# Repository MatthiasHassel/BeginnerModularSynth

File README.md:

# BeginnerModularSynth
DIY Modular Synth based on the Bela Board

I built this DIY Modular Synth for my bachelor thesis in February 2022. It is based on the Bela Board from the Augmented Instruments Laboratory in London and Eurorack compatible, where only voltages between 0V and +5V are evaluated correctly at the moment. However voltages beyond that limit won't harm the hardware and will be interpreted as 0V or +5V

With a "Default Patch" option it is possible to activate a fixed signal flow, where no patching is needed.

A lot of the code is inspired by materials based on a Master’s module “Music and Audio Programming”, taught by Dr Andrew McPherson in the School of Electronic Engineering and Computer Science. Thank you for making this lecture accessible for the public! 

C++ Realtime Programming with Bela:
https://www.youtube.com/watch?v=aVLRUyPBBJk&list=PLCrgFeG6pwQmdbB6l3ehC8oBBZbatVoz3

The Audio itself is not patchable for now, meaning the Audio signal flow is always Oscillator Out -> Filter In -> Filter Out -> Mixer In -> Mixer Out
For a next prototype however it is planned to change this to complete the modularity.

It's still a "work in progress" thing so I am happy about feedback and improvements!

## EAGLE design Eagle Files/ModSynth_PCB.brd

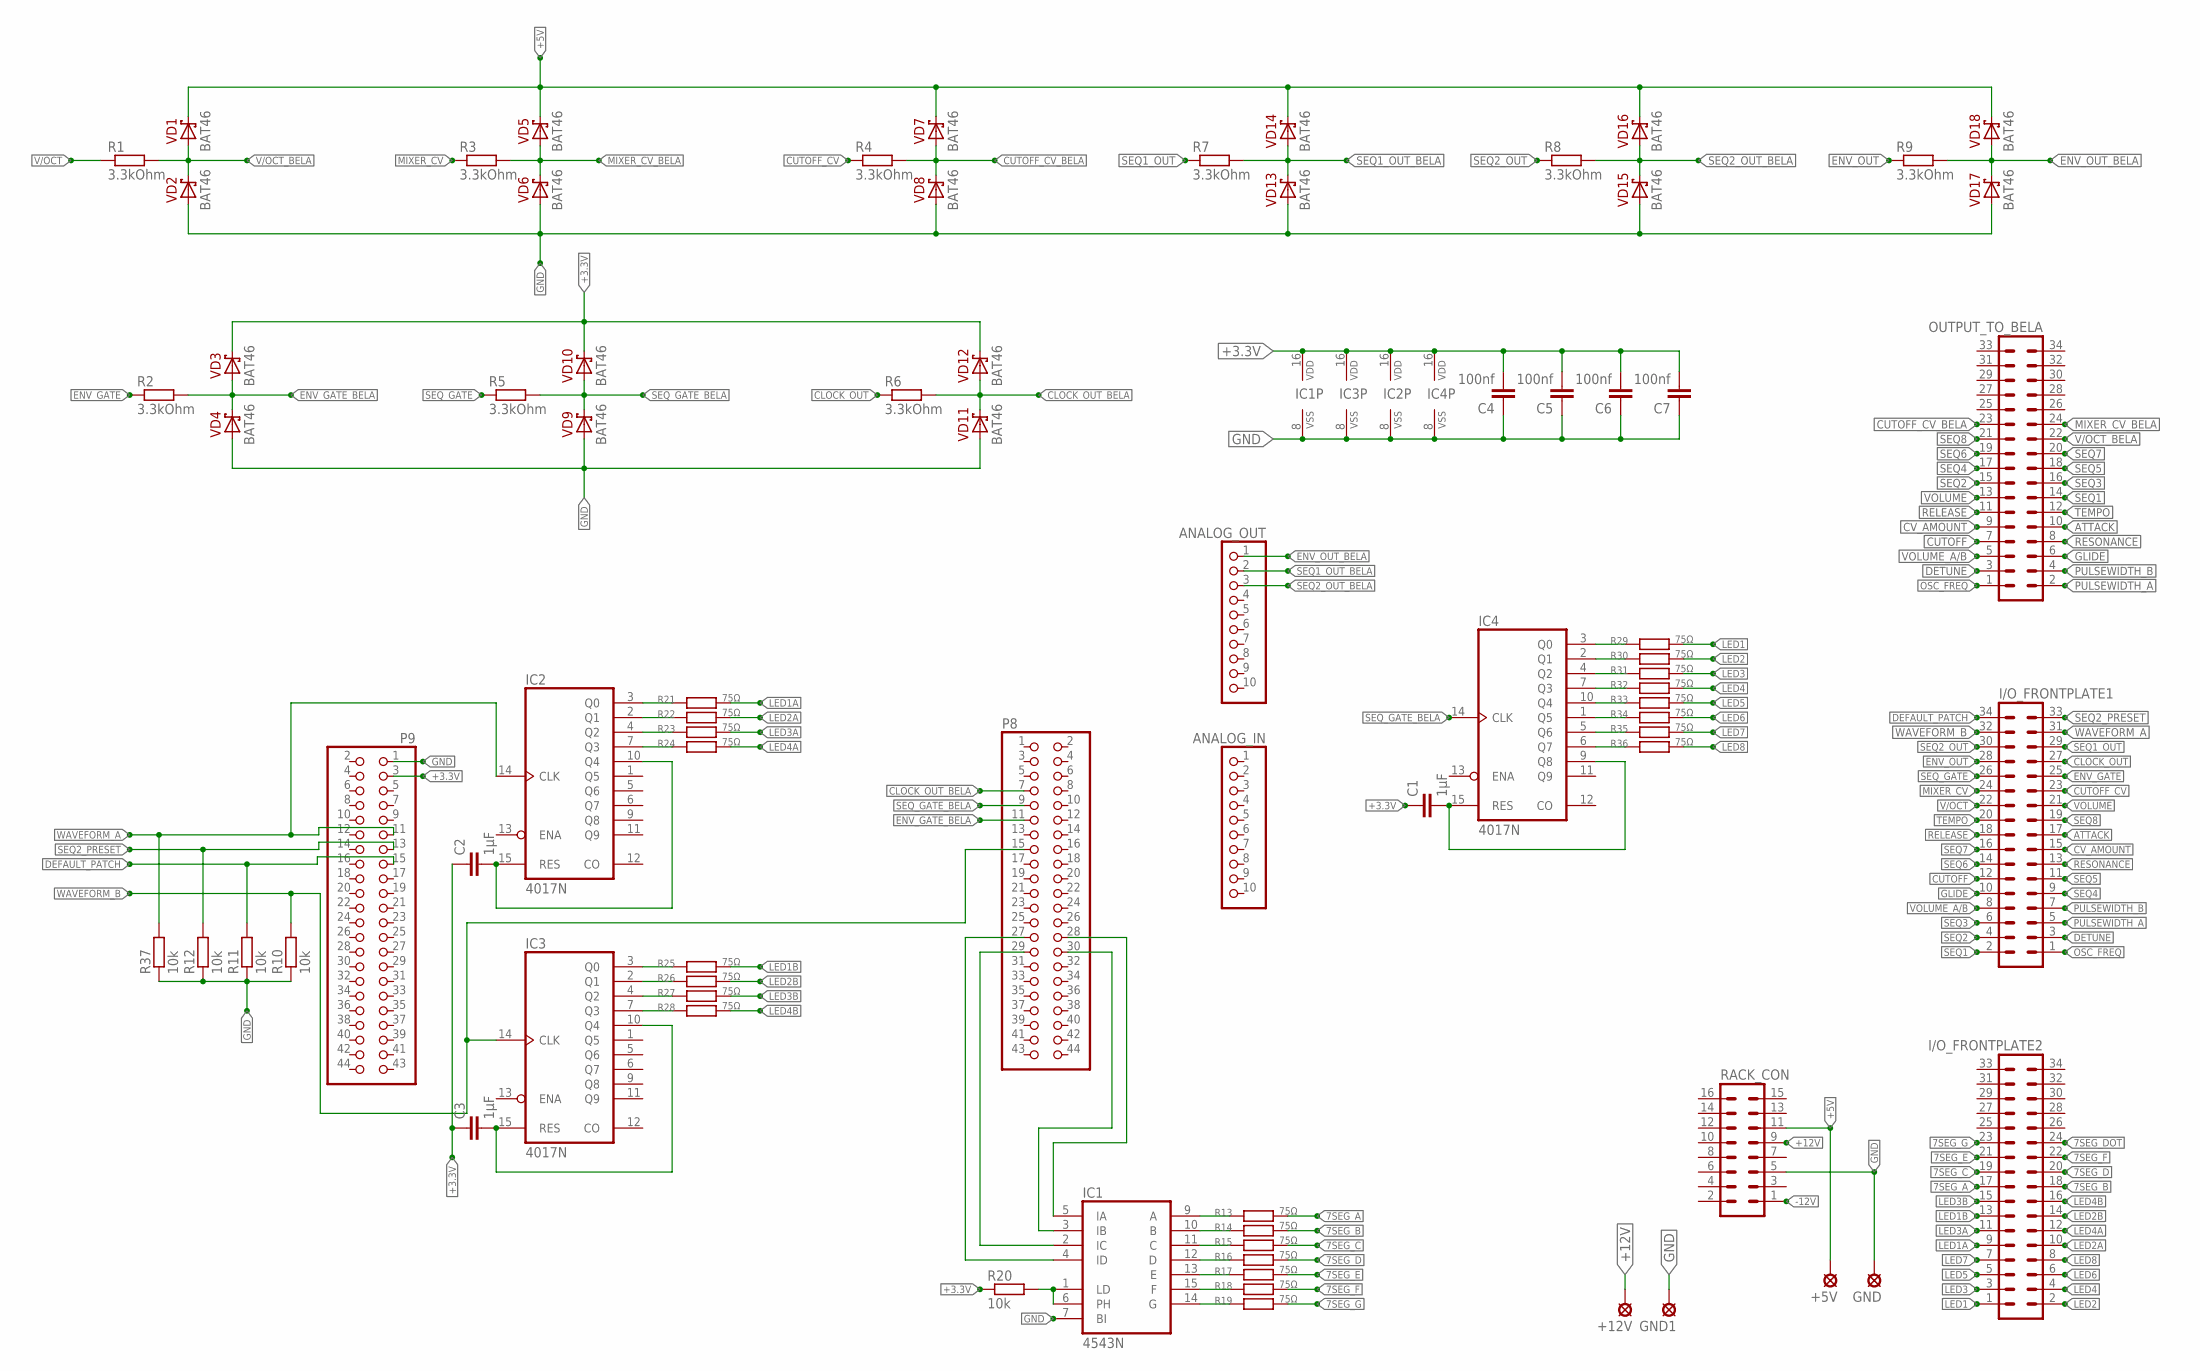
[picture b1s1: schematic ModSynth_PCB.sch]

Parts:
+5V, +12V: LSP10
ANALOG_IN: PINHD-1X10; 1X10
ANALOG_OUT: PINHD-1X10; 1X10
C1, C2, C3: 1µF; C025-025X050
C4, C5, C6, C7: 100nf; C025-025X050
GND, GND1: LSP10
I/O_FRONTPLATE1, I/O_FRONTPLATE2: ML34
IC1: 4543N; DIL16
IC2, IC3, IC4: 4017N; DIL16
OUTPUT_TO_BELA: ML34
P8, P9: PINHD-2X22; 2X22
R1, R2, R3, R4, R5, R6, R7, R8, R9: 3.3kOhm; 0204/7
R10, R11, R12, R20, R37: 10k; 0204/7
R13, R14, R15, R16, R17, R18, R19, R21, R22, R23, R24, R25, R26, R27, R28, R29, R30, R31, R32, R33, R34, R35, R36: 75Ω; 0204/7
RACK_CON: ML16
VD1, VD2, VD3, VD4, VD5, VD6, VD7, VD8, VD9, VD10, VD11, VD12, VD13, VD14, VD15, VD16, VD17, VD18: BAT46; DO35-7

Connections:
7SEG_A: I/O_FRONTPLATE2.17, R13.2
7SEG_B: I/O_FRONTPLATE2.18, R14.2
7SEG_C: I/O_FRONTPLATE2.19, R15.2
7SEG_D: I/O_FRONTPLATE2.20, R16.2
7SEG_DOT: I/O_FRONTPLATE2.24
7SEG_E: I/O_FRONTPLATE2.21, R17.2
7SEG_F: I/O_FRONTPLATE2.22, R18.2
7SEG_G: I/O_FRONTPLATE2.23, R19.2
+3.3V: C1.1, C2.1, C3.1, C4.2, C5.2, C6.2, C7.2, IC1.16 (VDD), IC2.16 (VDD), IC3.16 (VDD), IC4.16 (VDD), P9.3, R20.1, VD3.C, VD10.C, VD12.C
+5V: +5V.MP, RACK_CON.11, VD1.C, VD5.C, VD7.C, VD14.C, VD16.C, VD18.C
+12V: +12V.MP, RACK_CON.9
-12V: RACK_CON.1
ATTACK: I/O_FRONTPLATE1.17, OUTPUT_TO_BELA.10
CLOCK_OUT: I/O_FRONTPLATE1.27, R6.1
CLOCK_OUT_BELA: P8.7, R6.2, VD11.C, VD12.A
CUTOFF: I/O_FRONTPLATE1.12, OUTPUT_TO_BELA.7
CUTOFF_CV: I/O_FRONTPLATE1.23, R4.1
CUTOFF_CV_BELA: OUTPUT_TO_BELA.23, R4.2, VD7.A, VD8.C
CV_AMOUNT: I/O_FRONTPLATE1.15, OUTPUT_TO_BELA.9
DEFAULT_PATCH: I/O_FRONTPLATE1.34, P9.15, R11.2
DETUNE: I/O_FRONTPLATE1.3, OUTPUT_TO_BELA.3
ENV_GATE: I/O_FRONTPLATE1.25, R2.1
ENV_GATE_BELA: P8.11, R2.2, VD3.A, VD4.C
ENV_OUT: I/O_FRONTPLATE1.28, R9.1
ENV_OUT_BELA: ANALOG_OUT.1, R9.2, VD17.C, VD18.A
GLIDE: I/O_FRONTPLATE1.10, OUTPUT_TO_BELA.6
GND: C4.1, C5.1, C6.1, C7.1, GND.MP, GND1.MP, IC1.7 (BI), IC1.8 (VSS), IC2.8 (VSS), IC3.8 (VSS), IC4.8 (VSS), P9.1, R10.1, R11.1, R12.1, R37.1, RACK_CON.5, VD2.A, VD4.A, VD6.A, VD8.A, VD9.A, VD11.A, VD13.A, VD15.A, VD17.A
LED1: I/O_FRONTPLATE2.1, R29.2
LED1A: I/O_FRONTPLATE2.9, R21.2
LED1B: I/O_FRONTPLATE2.13, R25.2
LED2: I/O_FRONTPLATE2.2, R30.2
LED2A: I/O_FRONTPLATE2.10, R22.2
LED2B: I/O_FRONTPLATE2.14, R26.2
LED3: I/O_FRONTPLATE2.3, R31.2
LED3A: I/O_FRONTPLATE2.11, R23.2
LED3B: I/O_FRONTPLATE2.15, R27.2
LED4: I/O_FRONTPLATE2.4, R32.2
LED4A: I/O_FRONTPLATE2.12, R24.2
LED4B: I/O_FRONTPLATE2.16, R28.2
LED5: I/O_FRONTPLATE2.5, R33.2
LED6: I/O_FRONTPLATE2.6, R34.2
LED7: I/O_FRONTPLATE2.7, R35.2
LED8: I/O_FRONTPLATE2.8, R36.2
MIXER_CV: I/O_FRONTPLATE1.24, R3.1
MIXER_CV_BELA: OUTPUT_TO_BELA.24, R3.2, VD5.A, VD6.C
unnamed: IC1.9 (A), R13.1
unnamed: IC1.10 (B), R14.1
unnamed: IC1.11 (C), R15.1
unnamed: IC1.12 (D), R16.1
unnamed: IC1.13 (E), R17.1
unnamed: IC1.15 (F), R18.1
unnamed: IC1.14 (G), R19.1
unnamed: IC1.1 (LD), IC1.6 (PH), R20.2
unnamed: C2.2, IC2.10 (Q4), IC2.15 (RES)
unnamed: IC2.3 (Q0), R21.1
unnamed: IC2.2 (Q1), R22.1
unnamed: IC2.4 (Q2), R23.1
unnamed: IC2.7 (Q3), R24.1
unnamed: C3.2, IC3.10 (Q4), IC3.15 (RES)
unnamed: IC3.3 (Q0), R25.1
unnamed: IC3.2 (Q1), R26.1
unnamed: IC3.4 (Q2), R27.1
unnamed: IC3.7 (Q3), R28.1
unnamed: C1.2, IC4.9 (Q8), IC4.15 (RES)
unnamed: IC4.3 (Q0), R29.1
unnamed: IC4.2 (Q1), R30.1
unnamed: IC4.4 (Q2), R31.1
unnamed: IC4.7 (Q3), R32.1
unnamed: IC4.10 (Q4), R33.1
unnamed: IC4.1 (Q5), R34.1
unnamed: IC4.5 (Q6), R35.1
unnamed: IC4.6 (Q7), R36.1
unnamed: IC1.4 (ID), P8.27
unnamed: IC1.5 (IA), P8.28
unnamed: IC1.3 (IB), P8.30
unnamed: IC1.2 (IC), P8.29
OSC_FREQ: I/O_FRONTPLATE1.1, OUTPUT_TO_BELA.1
PULSEWIDTH_A: I/O_FRONTPLATE1.5, OUTPUT_TO_BELA.2
PULSEWIDTH_B: I/O_FRONTPLATE1.7, OUTPUT_TO_BELA.4
RELEASE: I/O_FRONTPLATE1.18, OUTPUT_TO_BELA.11
RESONANCE: I/O_FRONTPLATE1.13, OUTPUT_TO_BELA.8
SEQ1: I/O_FRONTPLATE1.2, OUTPUT_TO_BELA.14
SEQ1_OUT: I/O_FRONTPLATE1.29, R7.1
SEQ1_OUT_BELA: ANALOG_OUT.2, R7.2, VD13.C, VD14.A
SEQ2: I/O_FRONTPLATE1.4, OUTPUT_TO_BELA.15
SEQ2_OUT: I/O_FRONTPLATE1.30, R8.1
SEQ2_OUT_BELA: ANALOG_OUT.3, R8.2, VD15.C, VD16.A
SEQ2_PRESET: I/O_FRONTPLATE1.33, P9.13, R12.2
SEQ3: I/O_FRONTPLATE1.6, OUTPUT_TO_BELA.16
SEQ4: I/O_FRONTPLATE1.9, OUTPUT_TO_BELA.17
SEQ5: I/O_FRONTPLATE1.11, OUTPUT_TO_BELA.18
SEQ6: I/O_FRONTPLATE1.14, OUTPUT_TO_BELA.19
SEQ7: I/O_FRONTPLATE1.16, OUTPUT_TO_BELA.20
SEQ8: I/O_FRONTPLATE1.19, OUTPUT_TO_BELA.21
SEQ_GATE: I/O_FRONTPLATE1.26, R5.1
SEQ_GATE_BELA: IC4.14 (CLK), P8.9, R5.2, VD9.C, VD10.A
TEMPO: I/O_FRONTPLATE1.20, OUTPUT_TO_BELA.12
V/OCT: I/O_FRONTPLATE1.22, R1.1
V/OCT_BELA: OUTPUT_TO_BELA.22, R1.2, VD1.A, VD2.C
VOLUME: I/O_FRONTPLATE1.21, OUTPUT_TO_BELA.13
VOLUME_A/B: I/O_FRONTPLATE1.8, OUTPUT_TO_BELA.5
WAVEFORM_A: I/O_FRONTPLATE1.31, IC2.14 (CLK), P9.11, R37.2
WAVEFORM_B: I/O_FRONTPLATE1.32, IC3.14 (CLK), P8.15, R10.2

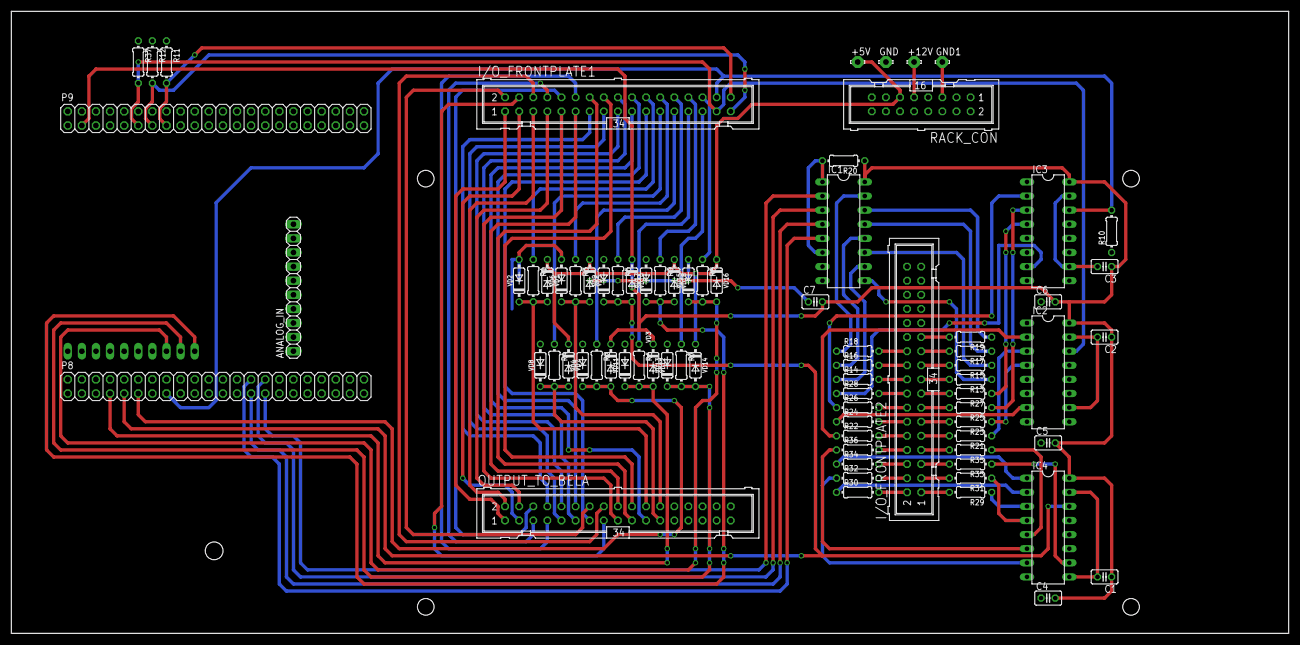
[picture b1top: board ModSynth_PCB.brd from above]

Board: 2 copper layers, 230.0 x 112.0 mm, 78 parts (1 on the bottom side), 101 nets.

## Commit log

2022-02-18 added additional files/infos
